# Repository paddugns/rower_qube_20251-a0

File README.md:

# Rower Qube 20251-A0

The ROWER QUBE 20251 is a custom RP2040-based development board designed for 
embedded system development, rapid prototyping, and educational applications. The board 
integrates the Raspberry Pi RP2040 microcontroller with essential support circuitry including 
external QSPI flash memory, USB connectivity, clock generation circuitry, power 
management, and GPIO expansion headers. 
The RP2040 microcontroller features a dual-core ARM Cortex-M0+ processor operating at 
frequencies up to 133 MHz. Combined with 16 MB of external flash memory, the board 
provides a reliable platform for firmware development, sensor interfacing, communication 
systems, and real-time control applications. 
The compact layout and straightforward programming method make the ROWER QUBE 
20251 suitable for students, hobbyists, researchers, and embedded system developers 
seeking a versatile RP2040 development platform. 

## Schematic Diagram
The schematic diagram of the ROWER QUBE 20251 development board illustrates 
the complete hardware implementation of the RP2040-based system. The design 
integrates the RP2040 microcontroller with supporting circuits including power 
management, external flash memory, clock generation, USB communication, 
BOOTSEL functionality, and GPIO expansion headers. 

The power section provides regulated 3.3 V operation from either a USB connection 
or an external power source. The flash memory subsystem provides non-volatile 
storage for firmware and application data, while the crystal oscillator ensures 
accurate clock generation for reliable system operation. GPIO header connectors 
expose the microcontroller pins for interfacing with external peripherals and 
expansion modules.

## 3D-View & PCB Layout
The three-dimensional representation of the ROWER QUBE 20251 development 
board provides a realistic view of component placement, connector orientation, and 
overall mechanical structure. The 3D model is generated directly from the PCB 
design data and serves as a valuable tool for validating component clearances, 
enclosure compatibility, and assembly requirements before fabrication.

The PCB layout of the ROWER QUBE 20251 development board was designed to 
provide reliable electrical performance, compact dimensions, and convenient access 
to all major interfaces. Special attention was given to component placement, power 
distribution, and signal routing to ensure stable operation of the RP2040 
microcontroller and associated circuitry. 
The board incorporates dedicated power and ground routing to minimize voltage 
drops and reduce electrical noise. Critical components such as the crystal oscillator, 
flash memory, and decoupling capacitors are placed close to the RP2040 
microcontroller to improve signal integrity and overall system reliability. 

## Gerber Images
Gerber file generation is a crucial step in the PCB manufacturing process, as it 
converts the completed PCB design into a standardized format that can be 
interpreted by fabrication machines. For the ROWER QUBE 20251 Development 
Board, Gerber files were generated using the KiCad PCB design software after 
completing the schematic design, PCB layout, and design rule verification. These files 
serve as the communication medium between the PCB designer and the 
manufacturing facility. 

The generated Gerber package includes all essential layers required for fabrication, 
such as the top and bottom copper layers, solder mask layers, silkscreen layers, 
paste layers, board outline, and drill files (Excellon format). Each layer contains 
precise information regarding track routing, pad locations, vias, component 
markings, and mechanical dimensions. This ensures that the fabricated board 
accurately matches the intended design specifications.

You can access the gerber images from the given zip file
[Gerber.zip](https://github.com/paddugns/rower_qube_20251-a0/blob/b17d841150b960b3ce6026f5780e1fa8d55f9cff/RQF%2020251/Soft%20copy/RQ-Datasheet.pdf)<br>

## Data Sheet
#### You can access the data sheet from the below link attached
[DataSheet.pdf](https://github.com/paddugns/rower_qube_20251-a0/blob/b17d841150b960b3ce6026f5780e1fa8d55f9cff/RQF%2020251/Soft%20copy/RQ-Datasheet.pdf)<br>

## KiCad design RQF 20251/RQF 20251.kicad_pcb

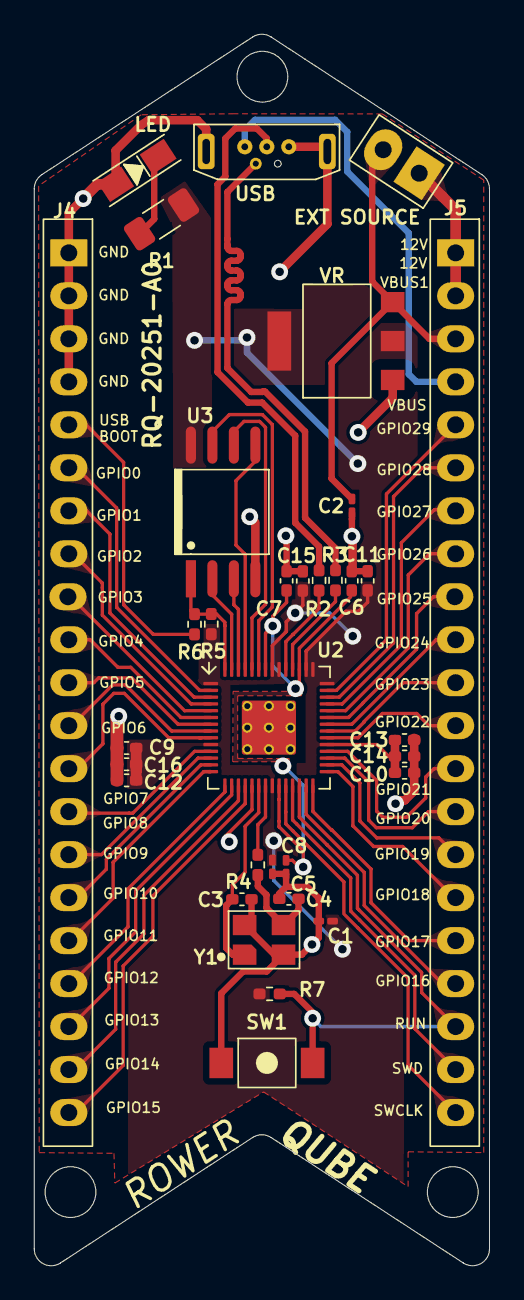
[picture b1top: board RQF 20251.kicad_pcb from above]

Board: 2 copper layers, 26.9 x 72.8 mm, 33 parts (0 on the bottom side), 54 nets.

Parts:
C1, C2: 10uF,0603; C_0201_0603Metric_Pad0.64x0.40mm_HandSolder
C3, C4: 15pF,0402; C_0402_1005Metric_Pad0.74x0.62mm_HandSolder
C5, C8: 1uF,0603; C_0201_0603Metric_Pad0.64x0.40mm_HandSolder
C6, C7, C9, C10, C11, C12, C13, C14, C15, C16: 100nF,0402; C_0402_1005Metric_Pad0.74x0.62mm_HandSolder
EXT SOURCE: 2.54x2; CONN-2.54X2
J4, J5: Conn_01x21; CONN-2X21
LED: green-3020; LED-3020
R1: 2K2,1206; R_1206_3216Metric_Pad1.30x1.75mm_HandSolder
R2, R3: 27E,0402; R_0402_1005Metric_Pad0.72x0.64mm_HandSolder
R4, R6, R7: 1k,0402; R_0402_1005Metric_Pad0.72x0.64mm_HandSolder
R5: 10k,0402; R_0402_1005Metric_Pad0.72x0.64mm_HandSolder
SW1: SW_SPST; TACT-SW-3X4X2
U2: RP2040; QFN-56
U3: W25Q128JVS; SOIC-8-208mil
USB: USB_B_Micro; USB3131-30-0230-A
VR: SOT-223-4
Y1: Crystal_GND24_Small; CRYSTAL-ABM8

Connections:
+1V1: C5.2, C6.2, C7.2, U2.23 (DVDD), U2.45 (VREG_VOUT), U2.50 (DVDD)
+3V3: C1.2, C8.1, C9.1, C10.1, C11.1, C12.1, C13.1, C14.1, C15.1, C16.1, R1.2, R5.1, R7.1, U2.1 (IOVDD), U2.10 (IOVDD), U2.22 (IOVDD), U2.33 (IOVDD), U2.42 (IOVDD), U2.43 (ADC_AVDD), U2.44 (VREG_IN), U2.48 (USB_VDD), U2.49 (IOVDD), U3.8 (VCC), VR.2 (O), VR.4 (O)
+12V: EXT SOURCE.1, J5.1, J5.2
/UD+: R2.2, U2.47 (USB_DP)
/UD-: R3.2, U2.46 (USB_DM)
GND: C1.1, C2.2, C3.2, C4.1, C5.1, C6.1, C7.1, C8.2, C9.2, C10.2, C11.2, C12.2, C13.2, C14.2, C15.2, C16.2, J4.1, J4.2, J4.3, J4.4, LED.1 (K), SW1.1 (A), U2.19 (TESTEN), U2.57 (GND), U3.4 (GND), USB.5 (GND), USB.6 (Shield), USB.7, VR.1 (G), Y1.2, Y1.4
GPIO0: J4.6, U2.2 (GPIO0)
GPIO1: J4.7, U2.3 (GPIO1)
GPIO2: J4.8, U2.4 (GPIO2)
GPIO3: J4.9, U2.5 (GPIO3)
GPIO4: J4.10, U2.6 (GPIO4)
GPIO5: J4.11, U2.7 (GPIO5)
GPIO6: J4.12, U2.8 (GPIO6)
GPIO7: J4.13, U2.9 (GPIO7)
GPIO8: J4.14, U2.11 (GPIO8)
GPIO9: J4.15, U2.12 (GPIO9)
GPIO10: J4.16, U2.13 (GPIO10)
GPIO11: J4.17, U2.14 (GPIO11)
GPIO12: J4.18, U2.15 (GPIO12)
GPIO13: J4.19, U2.16 (GPIO13)
GPIO14: J4.20, U2.17 (GPIO14)
GPIO15: J4.21, U2.18 (GPIO15)
GPIO16: J5.18, U2.27 (GPIO16)
GPIO17: J5.17, U2.28 (GPIO17)
GPIO18: J5.16, U2.29 (GPIO18)
GPIO19: J5.15, U2.30 (GPIO19)
GPIO20: J5.14, U2.31 (GPIO20)
GPIO21: J5.13, U2.32 (GPIO21)
GPIO22: J5.12, U2.34 (GPIO22)
GPIO23: J5.11, U2.35 (GPIO23)
GPIO24: J5.10, U2.36 (GPIO24)
GPIO25: J5.9, U2.37 (GPIO25)
GPIO26-ADC0: J5.8, U2.38 (GPIO26_ADC0)
GPIO27-ADC1: J5.7, U2.39 (GPIO27_ADC1)
GPIO28-ADC2: J5.6, U2.40 (GPIO28_ADC2)
GPIO29-ADC3: J5.5, U2.41 (GPIO29_ADC3)
unnamed: C4.2, R4.1, Y1.3
unnamed: LED.2 (A), R1.1
unnamed: U2.52 (QSPI_SCLK), U3.6 (CLK)
unnamed: U2.53 (QSPI_SD0), U3.5 (DI/IO_{0})
unnamed: U2.55 (QSPI_SD1), U3.2 (DO/IO_{1})
unnamed: U2.54 (QSPI_SD2), U3.3 (~WP/IO_{2})
unnamed: U2.51 (QSPI_SD3), U3.7 (~HOLD/~RESET/IO_{3})
unnamed: R5.2, R6.2, U2.56 (QSPI_SS), U3.1 (~CS)
unnamed: C3.1, U2.20 (XIN), Y1.1
unnamed: R4.2, U2.21 (XOUT)
RUN: J5.19, R7.2, SW1.2 (B), U2.26 (RUN)
SWCLK: J5.21, U2.24 (SWCLK)
SWD: J5.20, U2.25 (SWD)
USB-BOOT: J4.5, R6.1
USBD+: R2.1, USB.3 (D+)
USBD-: R3.1, USB.2 (D-)
VBUS: J5.4, USB.1 (VBUS)
VBUS1: C2.1, EXT SOURCE.2, J5.3, VR.3 (I)
